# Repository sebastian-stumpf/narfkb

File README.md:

# narfkb

[More pictures here](https://imgur.com/a/LNFxImS)

## Attention

I'm a hobbyist/amateur at best. So there may be things that aren't optimized. For example the routing on the PCB is a hot mess
and the spacers between the plate should be 3.4mm but there aren't any spacers that size. That being said I've had the files
in the `gerbers/` directory manufactured at JLC with 1.6mm size and they work just fine with the code provided in the `qmk/`
directory. So if you decide to use this, then please be advised that I'm not providing any sort of liability and you should
exercise some caution.

## BOM

| Quantity  | Item                               | Comment                  |
| --------- | ---------------------------------- | ------------------------ |
| 2         | Waveshare RP2040-Zero              |                          |
| 2         | IC-Sockets for MCU                 | Optional but recommended |
| 2         | TRRS Sockets                       |                          |
| 44        | 1N4148 SOD123 diodes               |                          |
| 30        | MX Hotswap Sockets                 |                          |
| 6         | Choc Hotswap Sockets               |                          |
| 2         | EC11 Encoders                      |                          |
| 6         | Omrom 6mm Tact switches            | B3F-1002                 |
| 30        | MX Switches + Keycaps              |                          |
| 6         | Choc Switches + Keycaps            |                          |
| 12        | M2 Screws, Nuts, Bolts and Spacers |                          |

## Feedback

I'm always happy to hear your opinions about this and if you decide to build this board then please do send me a picture of it.

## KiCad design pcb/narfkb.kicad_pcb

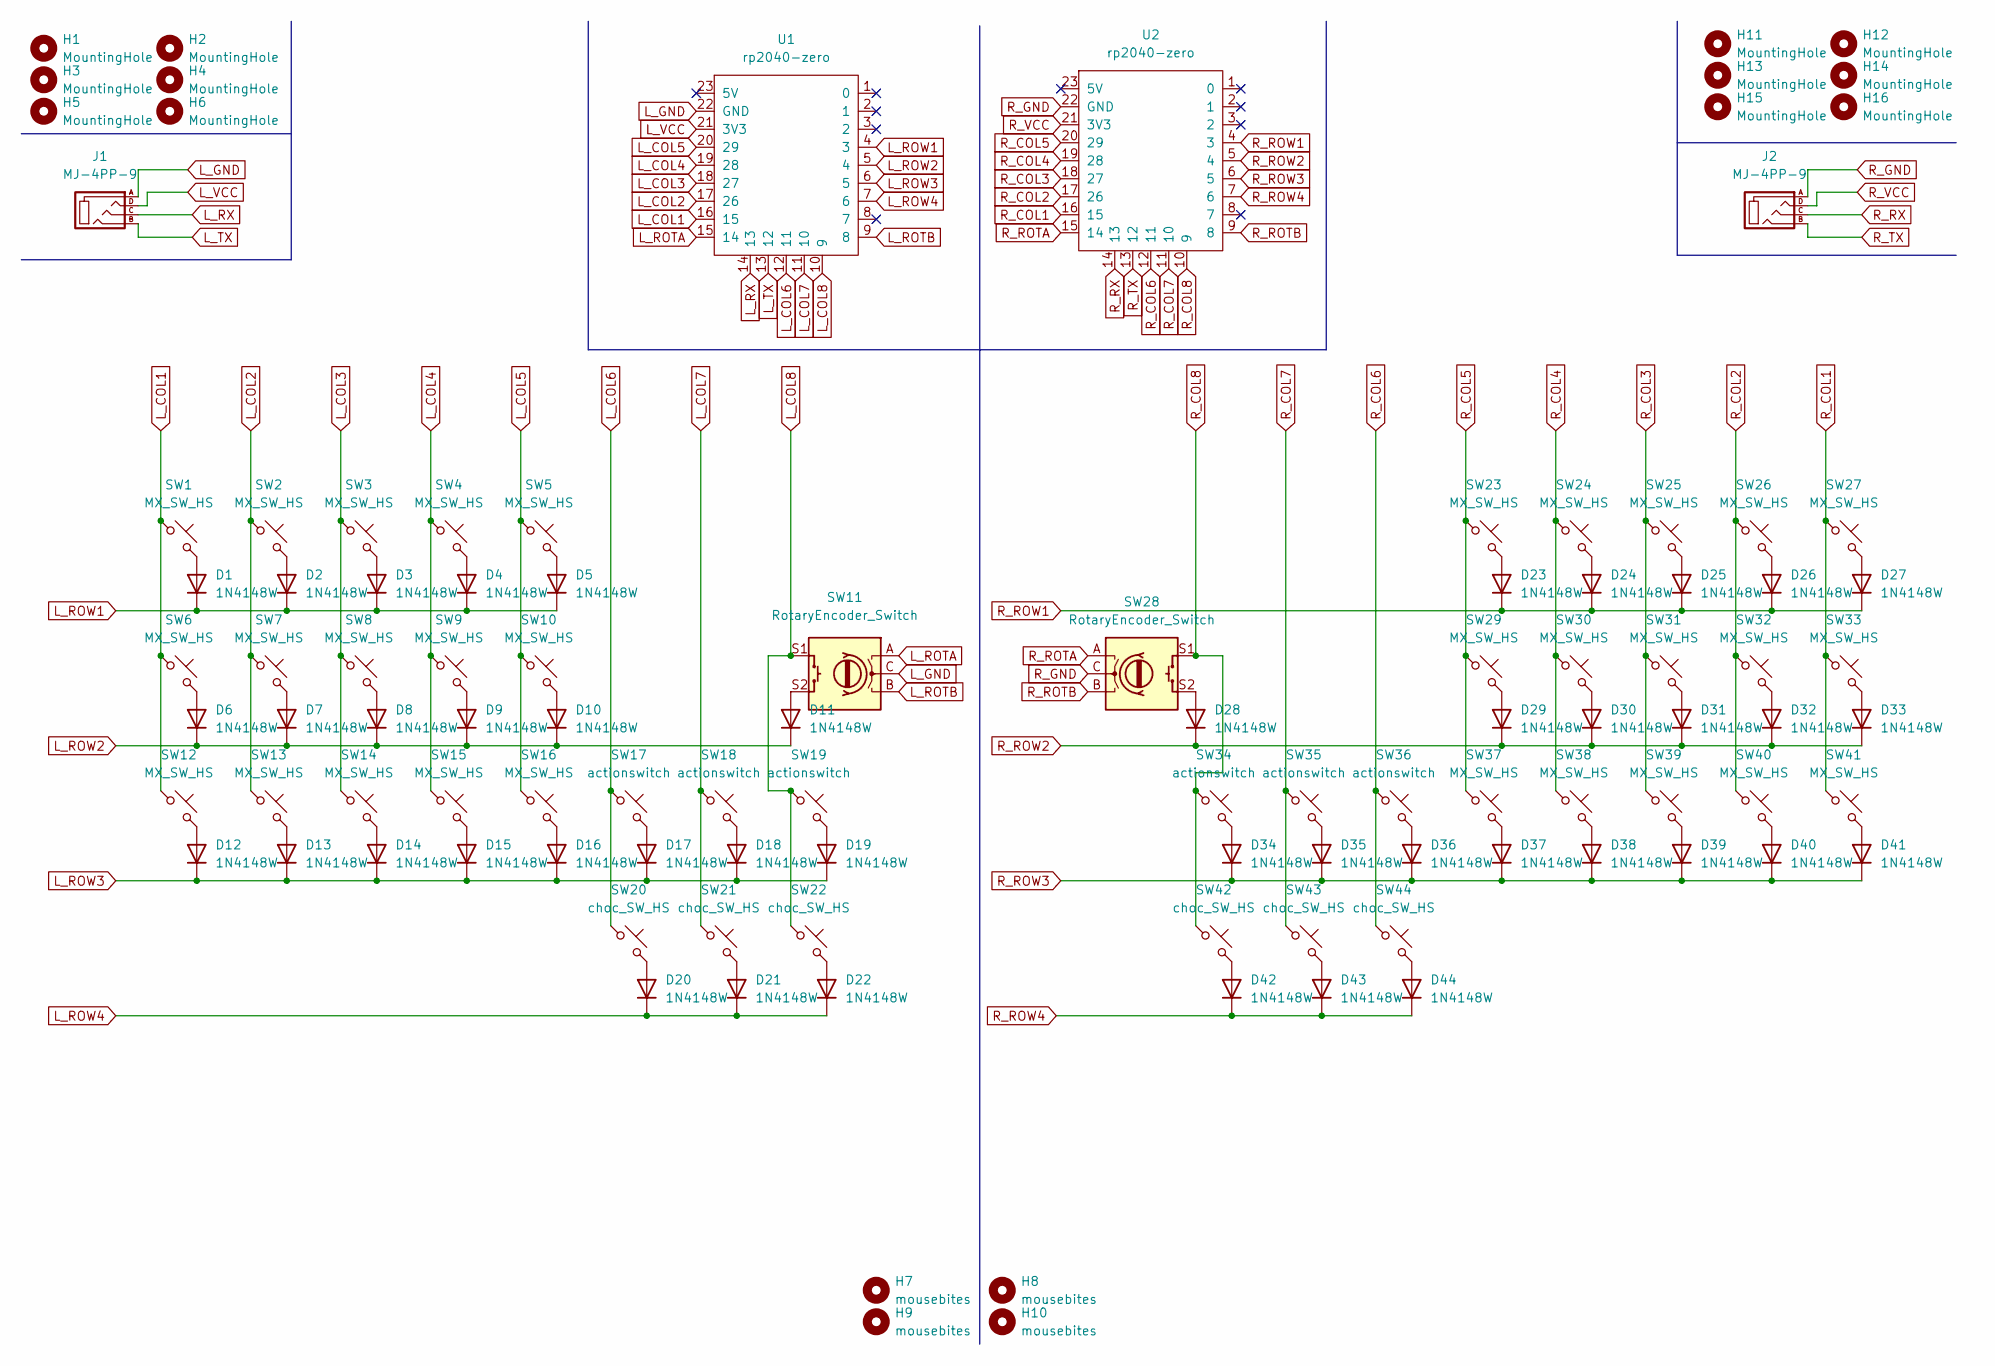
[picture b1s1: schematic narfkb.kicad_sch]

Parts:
D1, D2, D3, D4, D5, D6, D7, D8, D9, D10, D11, D12, D13, D14, D15, D16, D17, D18, D19, D20, D21, D22, D23, D24, D25, D26, D27, D28, D29, D30, D31, D32, D33, D34, D35, D36, D37, D38, D39, D40, D41, D42, D43, D44: 1N4148W; D_SOD-123
H1, H2, H3, H4, H5, H6, H11, H12, H13, H14, H15, H16: MountingHole; MountingHole_2.2mm_M2
H7, H8, H9, H10: mousebites; breakaway-mousebites
J1, J2: MJ-4PP-9
SW1, SW2, SW3, SW4, SW5, SW6, SW7, SW8, SW9, SW10, SW12, SW13, SW14, SW15, SW16, SW23, SW24, SW25, SW26, SW27, SW29, SW30, SW31, SW32, SW33, SW37, SW38, SW39, SW40, SW41: MX_SW_HS; SW_MX_HS_1u
SW11, SW28: RotaryEncoder_Switch; RotaryEncoder_EC11
SW17, SW18, SW19, SW34, SW35, SW36: actionswitch
SW20, SW21, SW22, SW42, SW43, SW44: choc_SW_HS; SW_choc_HS_1u
U1, U2: rp2040-zero; rp2040-zero-tht

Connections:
L_COL1: SW1.1, SW6.1, SW12.1, U1.16 (15)
L_COL2: SW2.1, SW7.1, SW13.1, U1.17 (26)
L_COL3: SW3.1, SW8.1, SW14.1, U1.18 (27)
L_COL4: SW4.1, SW9.1, SW15.1, U1.19 (28)
L_COL5: SW5.1, SW10.1, SW16.1, U1.20 (29)
L_COL6: SW17.1, SW20.1, U1.12 (11)
L_COL7: SW18.1, SW21.1, U1.11 (10)
L_COL8: SW11.S1, SW19.1, SW22.1, U1.10 (9)
L_GND: J1.A, SW11.C, U1.22 (GND)
L_ROTA: SW11.A, U1.15 (14)
L_ROTB: SW11.B, U1.9 (8)
L_ROW1: D1.1 (K), D2.1 (K), D3.1 (K), D4.1 (K), D5.1 (K), U1.4 (3)
L_ROW2: D6.1 (K), D7.1 (K), D8.1 (K), D9.1 (K), D10.1 (K), D11.1 (K), U1.5 (4)
L_ROW3: D12.1 (K), D13.1 (K), D14.1 (K), D15.1 (K), D16.1 (K), D17.1 (K), D18.1 (K), D19.1 (K), U1.6 (5)
L_ROW4: D20.1 (K), D21.1 (K), D22.1 (K), U1.7 (6)
L_RX: J1.C, U1.14 (13)
L_TX: J1.B, U1.13 (12)
L_VCC: J1.D, U1.21 (3V3)
unnamed: D1.2 (A), SW1.2
unnamed: D2.2 (A), SW2.2
unnamed: D3.2 (A), SW3.2
unnamed: D4.2 (A), SW4.2
unnamed: D5.2 (A), SW5.2
unnamed: D6.2 (A), SW6.2
unnamed: D7.2 (A), SW7.2
unnamed: D8.2 (A), SW8.2
unnamed: D9.2 (A), SW9.2
unnamed: D10.2 (A), SW10.2
unnamed: D11.2 (A), SW11.S2
unnamed: D12.2 (A), SW12.2
unnamed: D13.2 (A), SW13.2
unnamed: D14.2 (A), SW14.2
unnamed: D15.2 (A), SW15.2
unnamed: D16.2 (A), SW16.2
unnamed: D17.2 (A), SW17.2
unnamed: D18.2 (A), SW18.2
unnamed: D19.2 (A), SW19.2
unnamed: D20.2 (A), SW20.2
unnamed: D21.2 (A), SW21.2
unnamed: D22.2 (A), SW22.2
unnamed: D23.2 (A), SW23.2
unnamed: D24.2 (A), SW24.2
unnamed: D25.2 (A), SW25.2
unnamed: D26.2 (A), SW26.2
unnamed: D27.2 (A), SW27.2
unnamed: D28.2 (A), SW28.S2
unnamed: D29.2 (A), SW29.2
unnamed: D30.2 (A), SW30.2
unnamed: D31.2 (A), SW31.2
unnamed: D32.2 (A), SW32.2
unnamed: D33.2 (A), SW33.2
unnamed: D34.2 (A), SW34.2
unnamed: D35.2 (A), SW35.2
unnamed: D36.2 (A), SW36.2
unnamed: D37.2 (A), SW37.2
unnamed: D38.2 (A), SW38.2
unnamed: D39.2 (A), SW39.2
unnamed: D40.2 (A), SW40.2
unnamed: D41.2 (A), SW41.2
unnamed: D42.2 (A), SW42.2
unnamed: D43.2 (A), SW43.2
unnamed: D44.2 (A), SW44.2
R_COL1: SW27.1, SW33.1, SW41.1, U2.16 (15)
R_COL2: SW26.1, SW32.1, SW40.1, U2.17 (26)
R_COL3: SW25.1, SW31.1, SW39.1, U2.18 (27)
R_COL4: SW24.1, SW30.1, SW38.1, U2.19 (28)
R_COL5: SW23.1, SW29.1, SW37.1, U2.20 (29)
R_COL6: SW36.1, SW44.1, U2.12 (11)
R_COL7: SW35.1, SW43.1, U2.11 (10)
R_COL8: SW28.S1, SW34.1, SW42.1, U2.10 (9)
R_GND: J2.A, SW28.C, U2.22 (GND)
R_ROTA: SW28.A, U2.15 (14)
R_ROTB: SW28.B, U2.9 (8)
R_ROW1: D23.1 (K), D24.1 (K), D25.1 (K), D26.1 (K), D27.1 (K), U2.4 (3)
R_ROW2: D28.1 (K), D29.1 (K), D30.1 (K), D31.1 (K), D32.1 (K), D33.1 (K), U2.5 (4)
R_ROW3: D34.1 (K), D35.1 (K), D36.1 (K), D37.1 (K), D38.1 (K), D39.1 (K), D40.1 (K), D41.1 (K), U2.6 (5)
R_ROW4: D42.1 (K), D43.1 (K), D44.1 (K), U2.7 (6)
R_RX: J2.C, U2.14 (13)
R_TX: J2.B, U2.13 (12)
R_VCC: J2.D, U2.21 (3V3)

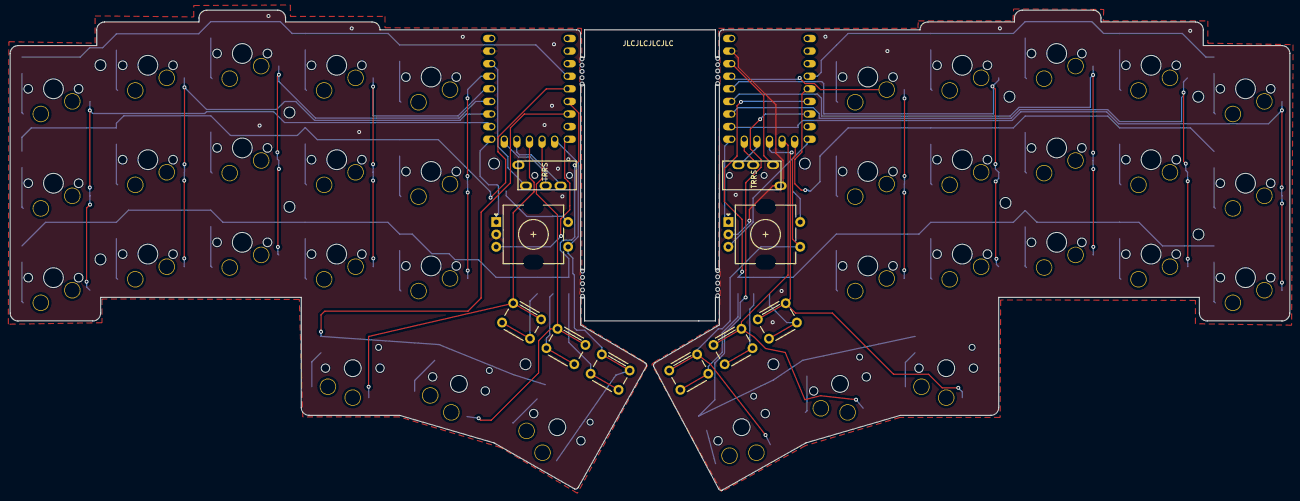
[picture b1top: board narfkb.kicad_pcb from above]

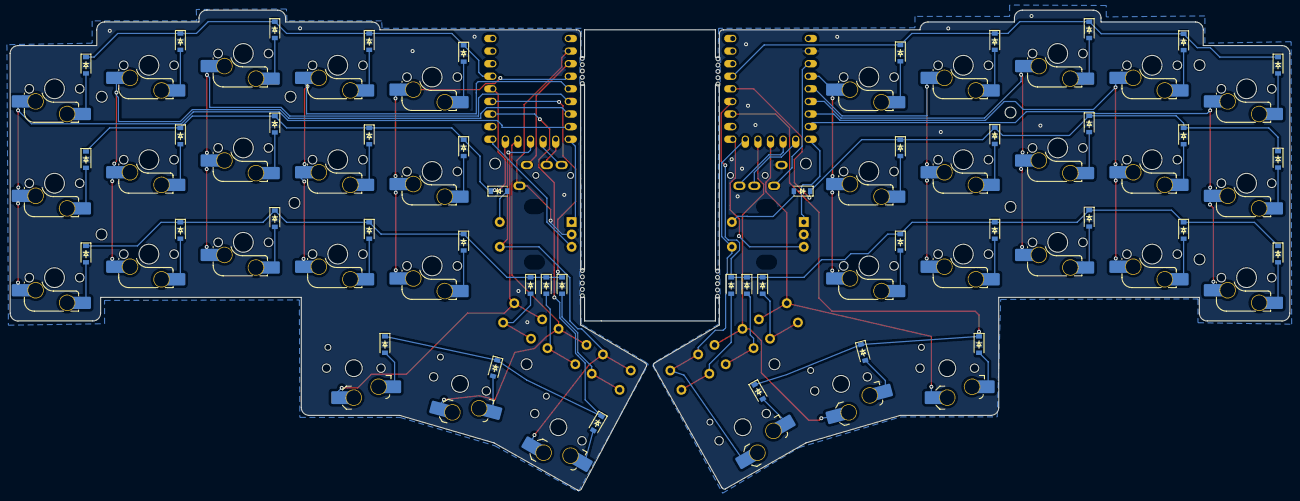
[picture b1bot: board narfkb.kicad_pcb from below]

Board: 2 copper layers, 258.2 x 96.9 mm, 108 parts (44 on the bottom side), 80 nets.

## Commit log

2023-04-01 added missing picture
2023-04-03 Update rules.mk
    moved bootloader and MCU to info.json
2023-04-03 Update info.json
    added bootloader, processor, and tags - to fall inline with QMK maintainers to partially modernise /keyboards to data driven format.
2023-04-07 Create LICENSE
2023-04-09 Add narfkb Keyboard
